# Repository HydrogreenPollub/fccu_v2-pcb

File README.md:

View this project on [CADLAB.io](https://cadlab.io/project/29095). 

# template-pcb

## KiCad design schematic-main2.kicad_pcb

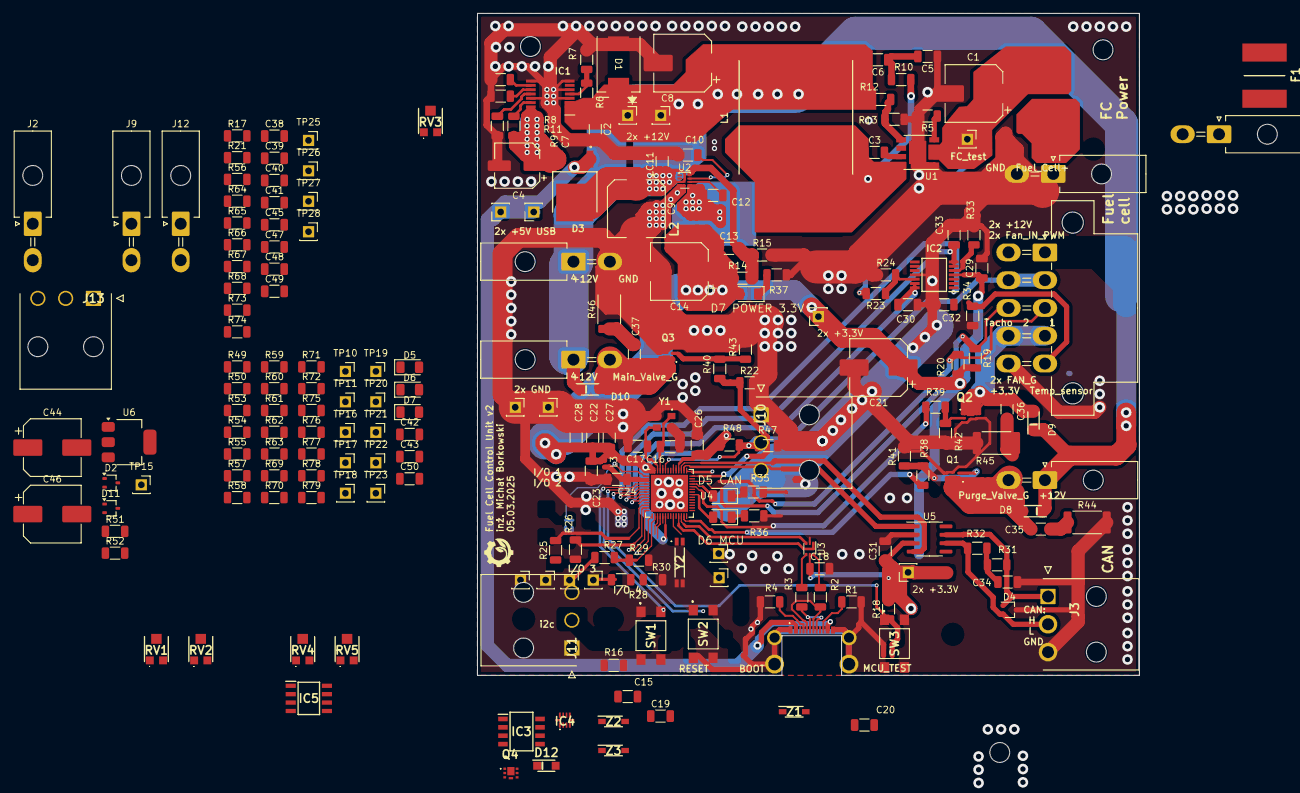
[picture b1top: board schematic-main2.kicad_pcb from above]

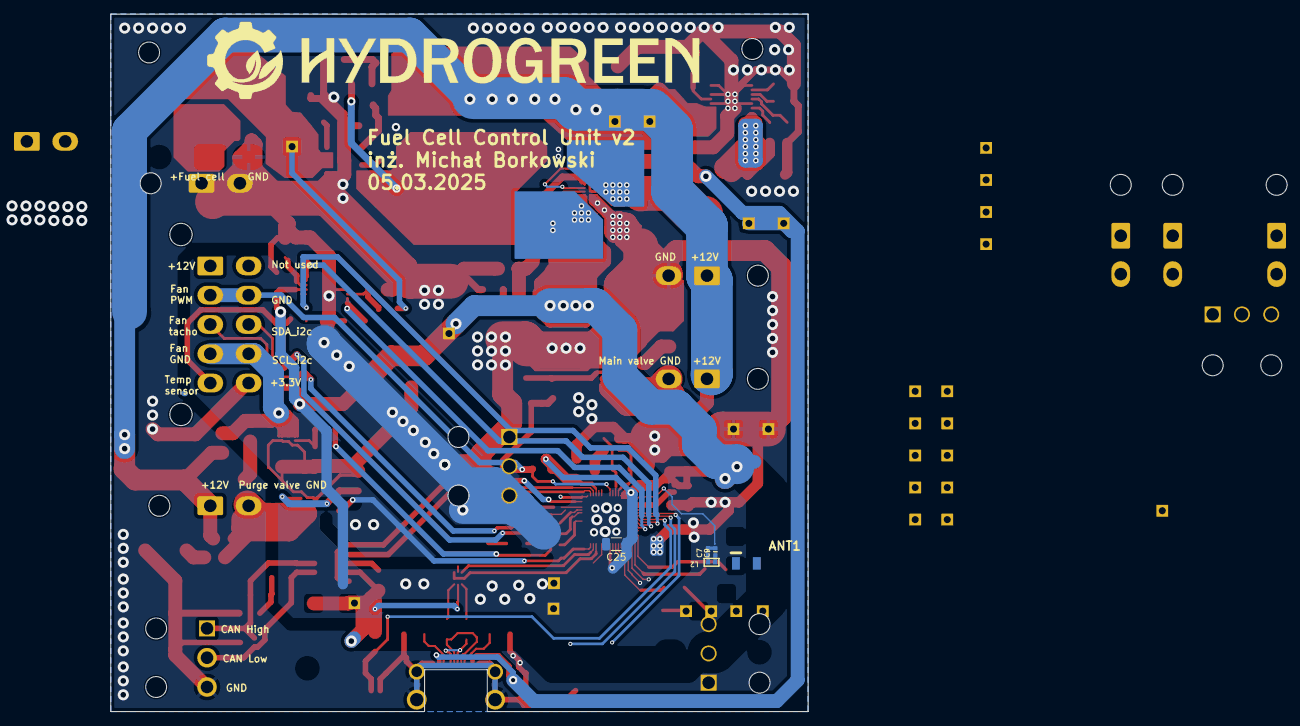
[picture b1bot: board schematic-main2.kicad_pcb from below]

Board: 2 copper layers, 100.0 x 100.0 mm, 224 parts (5 on the bottom side), 122 nets.

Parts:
ANT1: 2450AT18B100E; ANTC3216X140N
C1: 10u 100V; CP_Elec_8x10.5
C2, C22, C27, C39: 1u; C_1206_3216Metric
C3: 2n2 100V; C_1206_3216Metric
C4: 47u; CP_Elec_6.3x7.7
C5, C13: 47p; C_1206_3216Metric
C6: 3n3; C_1206_3216Metric
C7: 2n7; C_1206_3216Metric
C7#2: 2n7; _0402NO
C8, C44, C46: 22u; CP_Elec_8x10.5
C9, C21: 10u; CP_Elec_8x10.5
C9#2: 10u; _0402NO
C10: 33n; C_1206_3216Metric
C11, C12, C15, C18, C19, C20, C23, C24, C25, C26, C29, C31, C38, C43, C50: 100n; C_1206_3216Metric
C14: 100u; CP_Elec_8x10.5
C16, C17: 12p; C_1206_3216Metric
C28: 10n; C_1206_3216Metric
C30, C32, C33, C34, C42: 4n7; C_1206_3216Metric
C35, C36, C37: 20n; C_1206_3216Metric
C40, C41: 1p2; C_1206_3216Metric
C45, C47: 0; C_1206_3216Metric
C48, C49: 20p; C_1206_3216Metric
D1: TPSMC30CA; TPSMCSeries_LTF
D2, D11: V10K100DUHM3_H; SOT-323_SC-70
D3: V10K100DUHM3_H; TO252_(DPAK)_1
D4: SP0502BAJT; SOT-323_SC-70
D5, D5 CAN, D6, D6 MCU, D7, D7 POWER 3.3V: LED; LED_1206_3216Metric
D8, D9, D10: PMEG10020; PMEG10020ELR
D12: V10K100DUHM3_H; PMEG10020ELR
F1: 3A; FUSC8664X180N
IC1: LM76202QPWPRQ1; SOP65P640X120-17N
IC2: AD8544ARUZ-REEL; SOP65P640X120-14N
IC3: ILD206T; SOIC127P610X323-8N
IC4: TLA2024IRUGR; ADS7142IRUGT
IC5: 2EDN8534FXTMA1; SOIC127P602X173-8N
J1: Fuell_Cell; Molex_Mini-Fit_Jr_5569-02A2_2x01_P4.20mm_Horizontal
J2: Analog_In; Molex_Mini-Fit_Jr_5569-02A2_2x01_P4.20mm_Horizontal
J3: CAN; 39303035
J4: 12V_Out; Molex_Mini-Fit_Jr_5569-02A2_2x01_P4.20mm_Horizontal
J5, J9, J12: P_Valve; Molex_Mini-Fit_Jr_5569-02A2_2x01_P4.20mm_Horizontal
J6: M_Valve; Molex_Mini-Fit_Jr_5569-02A2_2x01_P4.20mm_Horizontal
J7: FC Cooling; Molex_Mini-Fit_Jr_5569-10A1_2x05_P4.20mm_Horizontal
J8: Supercapacitors; Molex_Mini-Fit_Jr_5569-02A2_2x01_P4.20mm_Horizontal
J10: UART; 39303035
J11: i2c; 39303035
J13: FC_Module; 39303035
L1: IHLP6767DZER470M11
L2: 4u7; SRN3015TA4R7M
L2#2: 4u7; _0402
L3: 2n; L_0402_1005Metric
P1: USB_C_Plug_USB2.0; 2169900002
Q1, Q2, Q3, Q4: PMPB10XNX; PMPB15XPAX
R1, R4: 5k1; R_1206_3216Metric
R2, R3: 0; R_1206_3216Metric
R5, R8, R9: 100k; R_1206_3216Metric
R6: 180k; R_1206_3216Metric
R7: 12k; R_1206_3216Metric
R10: 143k; R_1206_3216Metric
R11: 5k; R_1206_3216Metric
R12: 453k; R_1206_3216Metric
R13: 49k9; R_1206_3216Metric
R14: 47k; R_1206_3216Metric
R15, R34, R53, R54, R55, R79: 15k; R_1206_3216Metric
R16, R17, R18, R20, R22, R29, R30, R41, R42, R43, R47, R48, R56, R58, R59, R60, R61, R63, R66, R75, R76, R77, R78: 10k; R_1206_3216Metric
R19, R21, R74: 200R; R_1206_3216Metric
R23, R49: 6k8; R_1206_3216Metric
R24, R50: 3k3; R_1206_3216Metric
R25, R26, R33, R35, R36, R37, R69, R70, R71, R72: 1k; R_1206_3216Metric
R27, R28, R64, R65: 100R; R_1206_3216Metric
R31, R32: 60; R_1206_3216Metric
R38, R39, R40: 180R; R_1206_3216Metric
R44, R45, R46: 100R 0,5W; R_2512_6332Metric
R51, R52: 0R; R_1206_3216Metric
R57, R62: k; R_1206_3216Metric
R67, R68: 2k; R_1206_3216Metric
R73: 5M; R_1206_3216Metric
RV1: Pot_12V 20k; TC33X2503E
RV2: Pot_12V 5k; TC33X2503E
RV3, RV4, RV5: Pot_12V 2k; TC33X2503E
SW1, SW2, SW3: TL3305BF100QG; TL3305BF160QG
TP1, TP1#2, TP1#3, TP1#4: Vin test; PinSocket_1x01_P2.54mm_Vertical
TP2, TP2#2, TP3: GND; PinSocket_1x01_P2.54mm_Vertical
TP4, TP5: +12V; PinSocket_1x01_P2.54mm_Vertical
TP6, TP7: +5V; PinSocket_1x01_P2.54mm_Vertical
TP9, TP9#2: +3.3V; PinSocket_1x01_P2.54mm_Vertical
TP10: I/O 1; PinSocket_1x01_P2.54mm_Vertical
TP11: I/O 2; PinSocket_1x01_P2.54mm_Vertical
TP12: I/O 3; PinSocket_1x01_P2.54mm_Vertical
TP13: I/O 4; PinSocket_1x01_P2.54mm_Vertical
TP15: 5V; PinSocket_1x01_P2.54mm_Vertical
TP16: OP_1; PinSocket_1x01_P2.54mm_Vertical
TP17: OP_2; PinSocket_1x01_P2.54mm_Vertical
TP18: OP_3; PinSocket_1x01_P2.54mm_Vertical
TP19: OP_4; PinSocket_1x01_P2.54mm_Vertical
TP20: OP_8; PinSocket_1x01_P2.54mm_Vertical
TP21: OP_7; PinSocket_1x01_P2.54mm_Vertical
TP22: OP_6; PinSocket_1x01_P2.54mm_Vertical
TP23: OP_5; PinSocket_1x01_P2.54mm_Vertical
TP25: G14; PinSocket_1x01_P2.54mm_Vertical
TP26: G12; PinSocket_1x01_P2.54mm_Vertical
TP27: G42; PinSocket_1x01_P2.54mm_Vertical
TP28: G41; PinSocket_1x01_P2.54mm_Vertical
U1: LM5013DDAR; Diodes_SO-8EP
U2: TPS62933; SOT-583-8
U3: USBLC6-2P6; SOT-666
U4: ESP32-S3FN8; QFN-56-1EP_7x7mm_P0.4mm_EP5.6x5.6mm
U5: SN65HVD232; SOIC-8_3.9x4.9mm_P1.27mm
U6: LDI1117-05H; SOT-223-3_TabPin2
Y1: Crystal_GND24; KC3225K400000C1GE00
Y2: 9HT7-32.768KDZF-T; 9HT732768KDZFT
Z1, Z2, Z3: MMSZ3V3T1G; SOD3716X135N

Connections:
+3.3V: C13.1, C14.1, C18.1, C21.1, C22.1, C23.1, C25.1, C26.1, C27.1, C28.1, C29.1, C31.1, C38.1, C39.1, C43.1, C50.1, D7.2 (A), D7 POWER 3.3V.2 (A), IC2.4 (V+), IC4.8 (VDD), J2.1, L2.2, L2#2.2, L3.1, R14.1, R16.2, R17.2, R18.2, R20.2, R48.2, R59.1, R61.1, R67.2, R68.2, TP9.1, TP9#2.1, U3.5 (VBUS), U4.20 (VDD3P3_RTC), U4.29 (VDD_SPI), U4.46 (VDD3P3_CPU), U4.55 (VDDA), U4.56 (VDDA), U5.3 (VCC)
+5V: TP6.1, TP7.1, TP15.1
+12V: C2.1, C6.2, C8.1, D1.2 (A), D8.1 (K), D9.1 (K), D10.1 (K), IC1.1 (IN_1), IC1.2 (IN_2), IC1.3 (UVLO), J4.1, J5.1, J6.1, J7.1, L1.2, R6.1, R12.2, TP4.1, TP5.1
/IO/CANH: D4.1 (K), J3.1, R31.2, U5.7 (CANH)
/IO/CANL: D4.2 (K), J3.2, R32.2, U5.6 (CANL)
/IO/CAN_RX: U4.44 (MTCK/JTAG/GPIO39), U5.1 (D)
/IO/CAN_TX: U4.45 (MTDO/JTAG/GPIO40), U5.4 (R)
/IO/FAN_ON: C36.1, D9.2 (A), Q2.1 (D)
/IO/FC_V: J1.2, R23.2, R52.1
/IO/FC_VOLTAGE_MCU: C30.2, IC2.13 (-IN_D), IC2.14 (OUT_D)
/IO/I/O_3_MCU: R27.2, R29.1
/IO/I/O_4_MCU: R28.2, R30.1
/IO/LED_CAN_STATUS: D5.2 (A), D5 CAN.2 (A)
/IO/LED_MCU_STATUS: D6.2 (A), D6 MCU.2 (A)
/IO/LP_MCU: C32.2, IC2.1 (OUT_A), R57.1
/IO/Main_Valve: C37.1, D10.2 (A), J6.2, Q3.1 (D)
/IO/PURGE_VALVE: C35.1, D8.2 (A), J5.2, Q1.1 (D)
/IO/SC_VOLTAGE_MCU: C42.2, IC2.8 (OUT_C), IC2.9 (-IN_C)
/IO/TEMP_SENSOR: IC2.5 (+IN_B), R59.2
/IO/Temp_MCU: C33.1, IC2.7 (OUT_B), R60.2
/MCU/BOOT: C19.1, SW2.3 (K), SW2.4 (A), U4.5 (GPIO0/BOOT)
/MCU/BUTTON_MCU_G36: J9.1, R21.2
/MCU/FAN_IN_PWM_MCU_G45: R47.1, R48.1, R74.1
/MCU/MAIN_VALVE_MCU_G37: R22.1, U4.42 (GPIO37)
/MCU/MCU_TEST: C20.1, R56.2, SW3.1, SW3.2
/MCU/RESET: C15.1, R16.1, SW1.3 (K), SW1.4 (A), U4.4 (CHIP_PU/RESET)
/MCU/Rx_G44: J10.1, R65.2
/MCU/SCL_G10: J11.1, R68.1, U4.15 (GPIO10/ADC1_CH9)
/MCU/SDA_G9: J11.2, R67.1, U4.14 (GPIO9/ADC1_CH8)
/MCU/Tx_G43: J10.2, R64.1
/MCU/U1_VOLTAGE_G6: J12.1, R66.2
/MCU/USB_D+: R3.2, U3.3 (I/O2), U3.4 (I/O2), U4.26 (GPIO20/USB_D+/ADC2_CH9)
/MCU/USB_D-: R2.2, U3.1 (I/O1), U3.6 (I/O1), U4.25 (GPIO19/USB_D-/ADC2_CH8)
/MCU/XTAL_N: C16.1, U4.53 (XTAL_N), Y1.1
/MCU/XTAL_N_32: C48.1, R73.1, U4.22 (GPIO16/ADC2_CH5/XTAL_32K_N), Y2.4 (X2)
/MCU/XTAL_P: C17.1, U4.54 (XTAL_P), Y1.3
/MCU/XTAL_P_32: C49.1, R73.2, U4.21 (GPIO15/ADC2_CH4/XTAL_32K_P), Y2.1 (X1)
/Power /FB_12: RV1.2, U1.5 (FB)
/Power /Vreg: C4.1, C44.1, D11.1, D11.2, IC1.15 (OUT_1), IC1.16 (OUT_2), R9.1, U6.3 (VI)
/VBUS: D11.3, J8.2, P1.A4 (VBUS), P1.A9 (VBUS), P1.B4 (VBUS), P1.B9 (VBUS), R49.2, R51.1
GND: C1.2, C2.2, C4.2, C5.1, C7.2, C7#2.2, C8.2, C9.2, C9#2.2, C10.2, C11.2, C14.2, C15.2, C16.2, C17.2, C18.2, C19.2, C20.2, C21.2, C22.2, C23.2, C24.2, C25.2, C26.2, C27.2, C28.2, C29.2, C30.1, C31.2, C32.1, C33.2, C34.2, C38.2, C39.2, C40.1, C41.2, C42.1, C43.2, C44.2, C45.2, C46.2, C47.2, C48.2, C49.2, C50.2, D1.1 (K), D2.1, D2.2, D2.3, D4.3 (A), IC1.4 (NC_1), IC1.6 (MODE), IC1.8 (RTN), IC1.9 (GND), IC1.13 (NC_2), IC1.17 (EP), IC2.11 (GND), IC4.1 (ADDR), IC4.3 (GND), J1.1, J3.3, J4.2, J7.10, J8.1, J9.2, J10.3, J11.3, J12.2, P1.A1 (GND), P1.A12 (GND), P1.B1 (GND), P1.B12 (GND), Q1.3 (S), Q2.3 (S), Q3.3 (S), Q4.3 (S), R1.2, R4.2, R5.2, R7.2, R8.2, R11.2, R13.1, R15.2, R22.2, R24.1, R29.2, R30.2, R33.2, R34.2, R35.2, R36.2, R37.2, R41.2, R42.2, R43.2, R44.2, R45.2, R46.2, R47.2, R50.1, R53.2, R54.2, R55.2, R56.1, R58.2, R62.2, R79.2, SW1.1, SW1.2, SW2.1, SW2.2, TP2.1, TP2#2.1, TP3.1, U1.1 (GND), U1.9 (EP), U2.4 (GND), U3.2 (GND), U4.57 (GND), U5.2 (GND), U6.1 (GND), Y1.2, Y1.4, Y2.2 (GND_1), Y2.3 (GND_2), Z1.2 (A), Z2.2 (A), Z3.2 (A)
unnamed: ANT1.1 (FEED), C40.2
unnamed: C5.2, C6.1, R10.2
unnamed: C34.1, R31.1, R32.1
unnamed: C35.2, R44.1
unnamed: C36.2, R45.1
unnamed: C37.2, R46.1
unnamed: D3.1, D3.2, R52.2
unnamed: D3.3, R51.2
unnamed: D5.1 (K), D5 CAN.1 (K), R35.1
unnamed: D6.1 (K), D6 MCU.1 (K), R36.1
unnamed: D7.1 (K), D7 POWER 3.3V.1 (K), R37.1
unnamed: C7.1, C7#2.1, IC1.12 (DVDT)
unnamed: IC1.11 (ILIM), RV3.2
unnamed: IC1.10 (IMON), R8.1
unnamed: IC1.5 (OVP), R6.2, R7.1
unnamed: IC1.14 (~FLT), R9.2
unnamed: IC2.3 (+IN_A), R34.1, R63.2
unnamed: IC2.10 (+IN_C), RV4.2
unnamed: IC2.12 (+IN_D), RV5.2
unnamed: IC2.2 (-IN_A), R57.2, R62.1
unnamed: IC2.6 (-IN_B), R58.1, R60.1
unnamed: IC3.1 (A_1), R69.2
unnamed: IC3.3 (A_2), R70.2
unnamed: IC3.6 (C_3), R72.1
unnamed: IC3.8 (C_4), R71.1
unnamed: IC3.5 (E_1), TP23.1
unnamed: IC3.7 (E_2), TP21.1
unnamed: IC3.2 (K_1), TP17.1
unnamed: IC3.4 (K_2), TP19.1
unnamed: IC4.4 (AIN0), R78.2, R79.1
unnamed: IC4.5 (AIN1), R53.1, R75.2
unnamed: IC4.6 (AIN2), R54.1, R76.2
unnamed: IC4.7 (AIN3), R55.1, R77.2
unnamed: P1.A5 (CC), R4.1
unnamed: P1.A6 (D+), P1.B6 (D+), R3.1
unnamed: P1.A7 (D-), P1.B7 (D-), R2.1
unnamed: P1.B5 (VCONN), R1.1
unnamed: Q1.2 (G), R38.1, R41.1
unnamed: Q2.2 (G), R39.1, R42.1
unnamed: Q3.2 (G), R40.1, R43.1
unnamed: R11.1, RV3.1
unnamed: R12.1, RV1.3
unnamed: R13.2, RV1.1
unnamed: R14.2, RV2.3
unnamed: R15.1, RV2.1
unnamed: R23.1, RV5.1
unnamed: R24.2, RV5.3
unnamed: R25.1, TP10.1
unnamed: R26.1, TP11.1
unnamed: R27.1, TP12.1
unnamed: R28.1, TP13.1
unnamed: R33.1, R61.2
unnamed: R49.1, RV4.1
unnamed: R50.2, RV4.3
unnamed: R69.1, TP16.1
unnamed: R70.1, TP18.1
unnamed: R71.2, TP20.1
unnamed: R72.2, TP22.1
unnamed: R18.1, SW3.3 (K), SW3.4 (A)
unnamed: C3.2, U1.7 (BST)
unnamed: C1.1, F1.2, TP1.1, TP1#2.1, TP1#3.1, TP1#4.1, U1.2 (VIN), U1.3 (EN_UVLO)
unnamed: R5.1, U1.4 (RON)
unnamed: C3.1, L1.1, R10.1, U1.8 (SW)
unnamed: C12.1, U2.6 (BST)
unnamed: C13.2, RV2.2, U2.8 (FB)
unnamed: C10.1, U2.7 (SS)
unnamed: C12.2, L2.1, L2#2.1, U2.5 (SW)
unnamed: C9.1, C9#2.1, C11.1, U2.3 (VIN)
unnamed: C45.1, R66.1, U4.11 (GPIO6/ADC1_CH5), Z2.1 (K)
unnamed: TP26.1, U4.17 (GPIO12/ADC2_CH1)
unnamed: TP25.1, U4.19 (GPIO14/ADC2_CH3)
unnamed: R17.1, R19.1, U4.40 (GPIO35), Z3.1 (K)
unnamed: C47.1, R20.1, R21.1, U4.41 (GPIO36), Z1.1 (K)
unnamed: R74.2, U4.51 (GPIO45)
unnamed: C41.1, U4.1 (LNA_IN/RF)
unnamed: TP28.1, U4.47 (MTDI/JTAG/GPIO41)
unnamed: TP27.1, U4.48 (MTMS/JTAG/GPIO42)
unnamed: R65.1, U4.50 (U0RXD/PROG/GPIO44)
unnamed: R64.2, U4.49 (U0TXD/PROG/GPIO43)
unnamed: C46.1, D12.1, D12.2, U6.2 (VO)
VDD3P3: C24.1, L3.2, U4.2 (VDD3P3), U4.3 (VDD3P3)

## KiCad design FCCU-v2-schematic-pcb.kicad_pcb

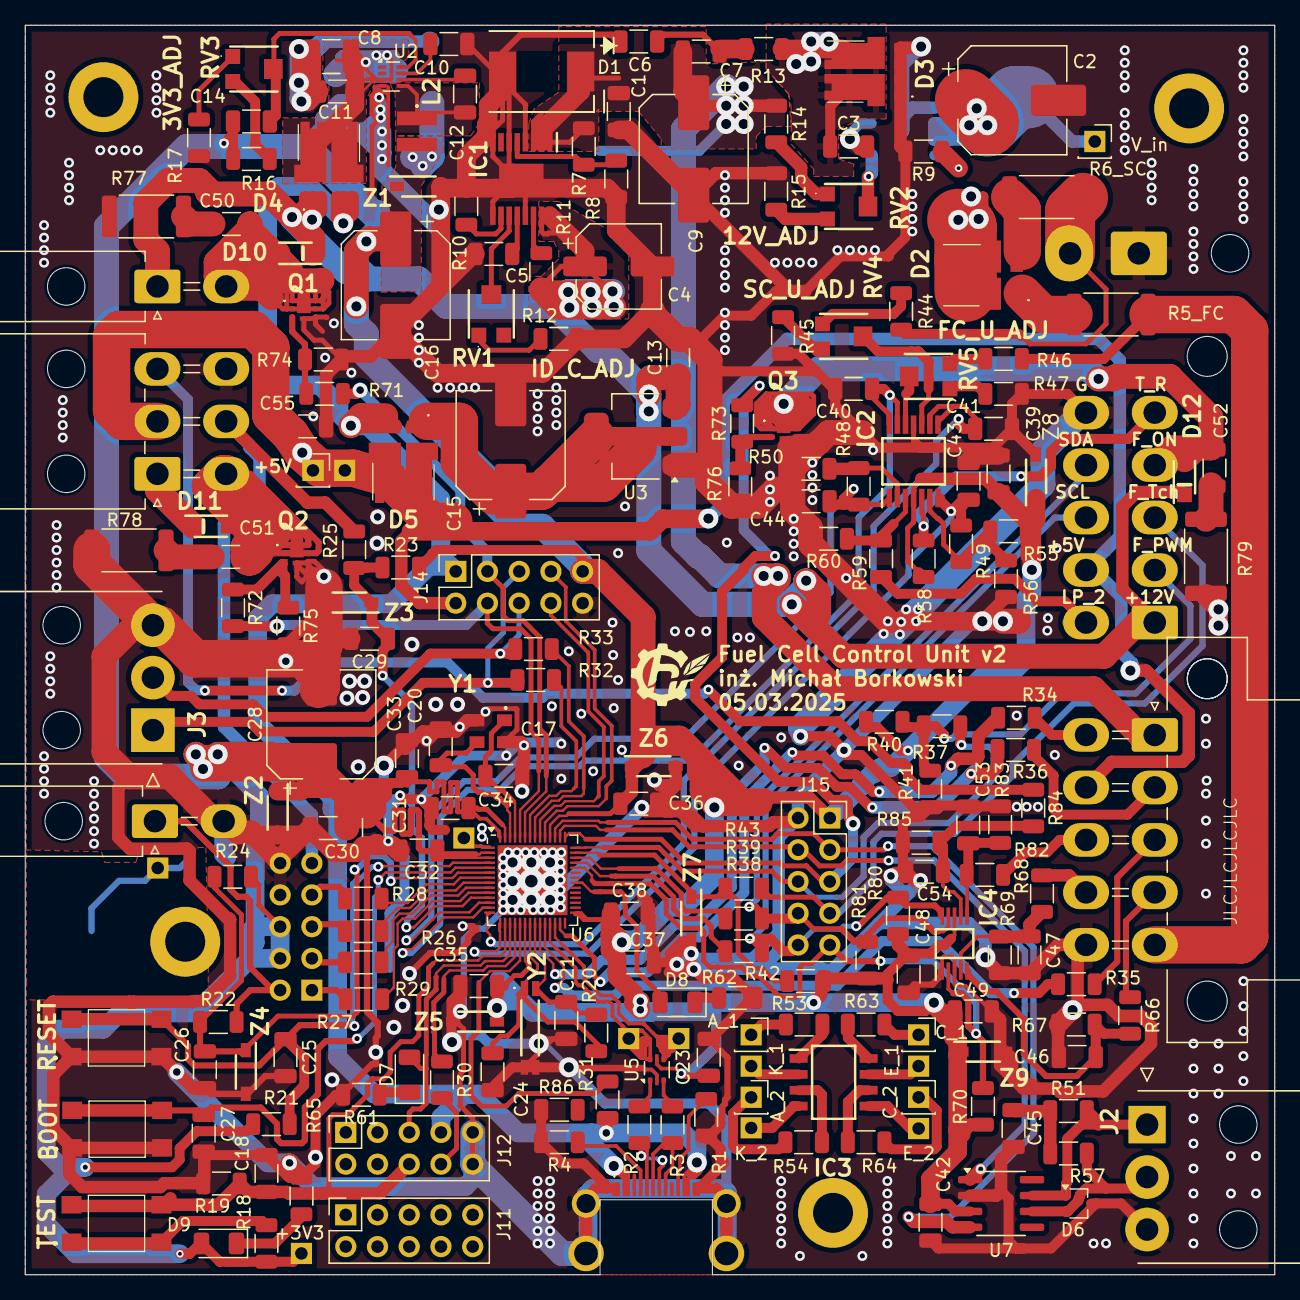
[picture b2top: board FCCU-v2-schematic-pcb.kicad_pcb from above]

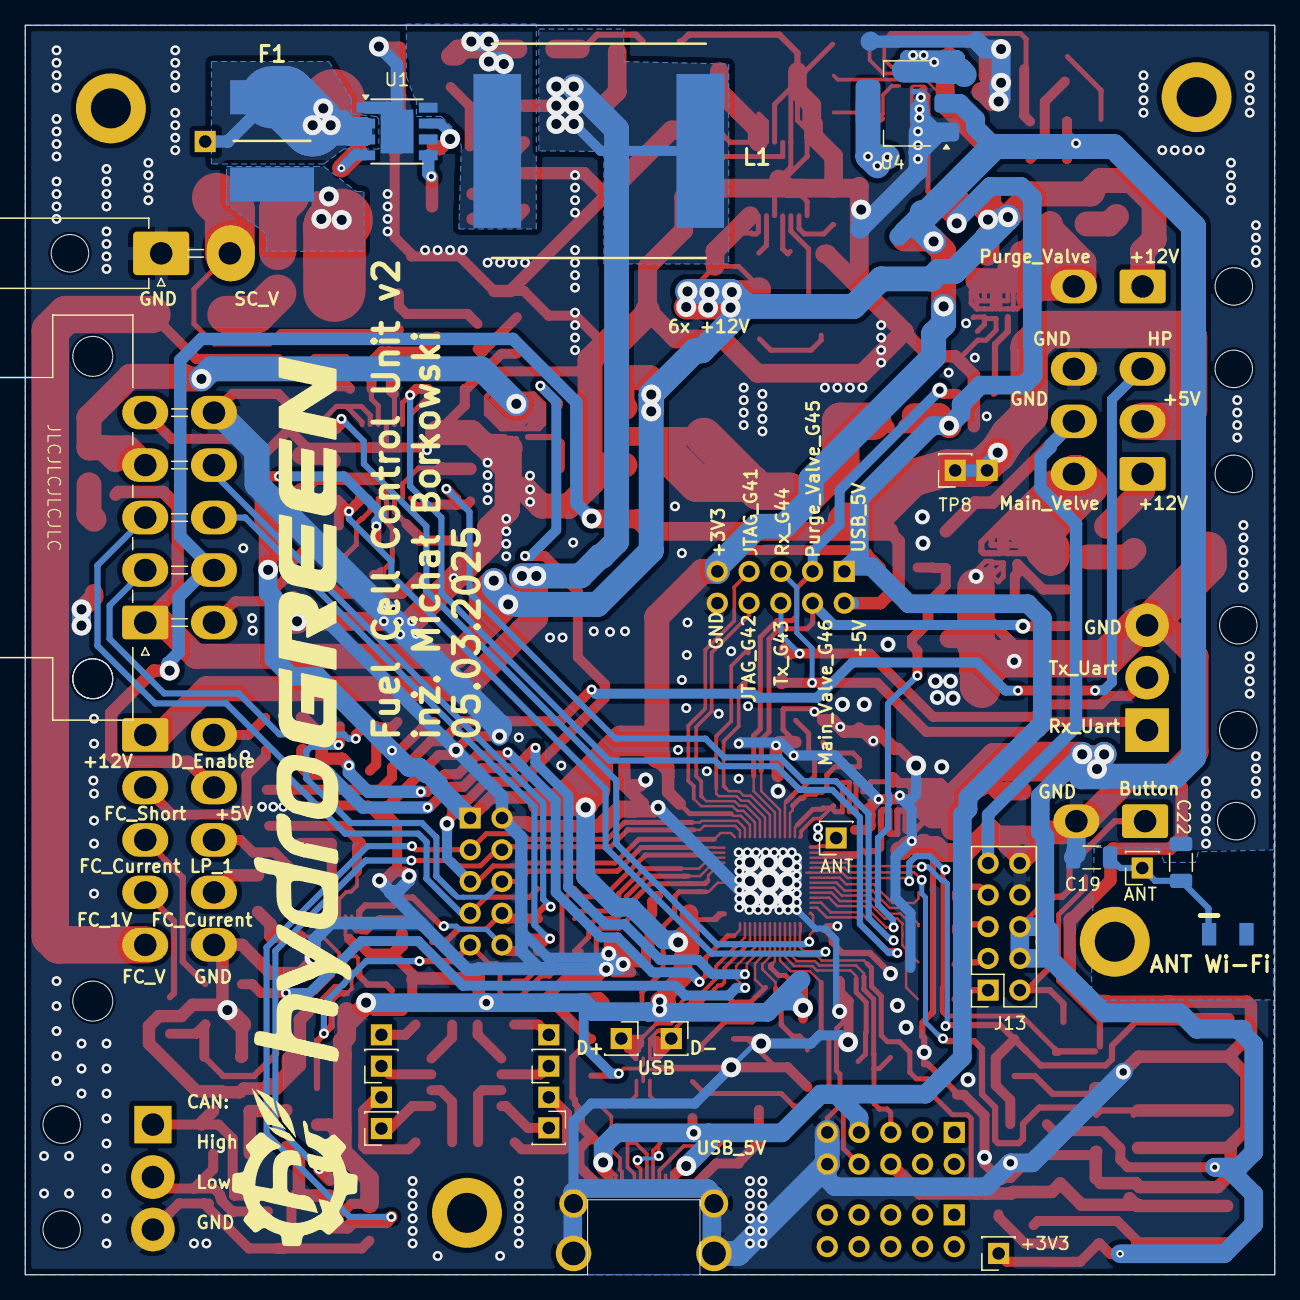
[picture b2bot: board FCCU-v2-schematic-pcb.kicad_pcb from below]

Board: 2 copper layers, 100.0 x 100.0 mm, 219 parts (20 on the bottom side), 142 nets.

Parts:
+3V3: +3.3V; PinSocket_1x01_P2.54mm_Vertical
+5V: +5V; PinSocket_1x01_P2.54mm_Vertical
ANT: Ant; PinSocket_1x01_P2.54mm_Vertical
ANT Wi-Fi: 2450AT18B100E; ANTC3216X140N
A_1: A_1; PinSocket_1x01_P2.54mm_Vertical
A_2: A_2; PinSocket_1x01_P2.54mm_Vertical
BOOT: TL3305BF100QG; TL3305BF160QG
C1, C13, C30, C33, C38, C55: 1u; C_1206_3216Metric
C2: 10u 100V; CP_Elec_8x10.5
C3: 2n2 100V; C_1206_3216Metric
C4: 47u; CP_Elec_6.3x7.7
C5: 2n7; C_1206_3216Metric
C6, C14: 47p; C_1206_3216Metric
C7: 3n3; C_1206_3216Metric
C8: 1-10u; C_1210_3225Metric_Pad1.33x2.70mm_HandSolder
C9, C15: 22u; CP_Elec_8x10.5
C10: 33n; C_1206_3216Metric
C11, C12, C18, C23, C25, C27, C31, C32, C35, C36, C37, C39, C42, C48: 100n; C_1206_3216Metric
C16: 100u; CP_Elec_8x10.5
C17, C20: 12p; C_1206_3216Metric
C19, C22: 1p2; C_1206_3216Metric
C21, C24: 20p; C_1206_3216Metric
C26, C29: 0; C_1206_3216Metric
C28: 10u; CP_Elec_8x10.5
C34: 10n; C_1206_3216Metric
C40, C41, C44, C46, C47, C53, C54: c; C_1206_3216Metric
C43, C45: 4n7; C_1206_3216Metric
C49: 4N7; C_1206_3216Metric
C50, C51, C52: 20n; C_1206_3216Metric
C_1: C_1; PinSocket_1x01_P2.54mm_Vertical
C_2: C_2; PinSocket_1x01_P2.54mm_Vertical
D1: TPSMC30CA; TPSMCSeries_LTF
D2, D3, D4, D5: V10K100DUHM3_H; V10K100DUHM3H
D6: SP0502BAJT; SOT-323_SC-70
D7, D8, D9: LED; LED_1206_3216Metric
D10, D11, D12: PMEG10020; PMEG10020ELR
E_1: E_1; PinSocket_1x01_P2.54mm_Vertical
E_2: E_2; PinSocket_1x01_P2.54mm_Vertical
F1: 3A; FUSC8664X180N
IC1: LM76202QPWPRQ1; SOP65P640X120-17N
IC2: AD8544ARUZ-REEL; SOP65P640X120-14N
IC3: ILD206T; SOIC127P610X323-8N
IC4: ADS1015IDGSR; SOP50P490X110-10N
J1: Supercapacitors; Molex_Mini-Fit_Jr_5569-02A2_2x01_P4.20mm_Horizontal
J2: CAN; 39303035
J3: UART; 39303035
J4: P_Valve; Molex_Mini-Fit_Jr_5569-02A2_2x01_P4.20mm_Horizontal
J5: Button; Molex_Mini-Fit_Jr_5569-02A2_2x01_P4.20mm_Horizontal
J6: FC Module; Molex_Mini-Fit_Jr_5569-10A1_2x05_P4.20mm_Horizontal
J7: FC Cooling; Molex_Mini-Fit_Jr_5569-10A1_2x05_P4.20mm_Horizontal
J8: M_Valve; Molex_Mini-Fit_Jr_5569-06A2_2x03_P4.20mm_Horizontal
J11: NC; PinSocket_2x05_P2.54mm_Vertical
J12: Analog; PinSocket_2x05_P2.54mm_Vertical
J13: I/O; PinSocket_2x05_P2.54mm_Vertical
J14: Top signals; PinSocket_2x05_P2.54mm_Vertical
J15: Fuel cell signals; PinSocket_2x05_P2.54mm_Vertical
K_1: K_1; PinSocket_1x01_P2.54mm_Vertical
K_2: K_2; PinSocket_1x01_P2.54mm_Vertical
L1: IHLP6767DZER470M11
L2: 4u7; SRN3015TA4R7M
P1: USB_C_Plug_USB2.0; 2169900002
Q1, Q2, Q3: PMPB10XNX; PMPB15XPAX
R1, R4: 5k1; R_1206_3216Metric
R2, R3: 0; R_1206_3216Metric
R5_FC, R6_SC: 0R; R_2512_6332Metric
R7: 180k; R_1206_3216Metric
R8: 12k; R_1206_3216Metric
R9, R10, R11: 100k; R_1206_3216Metric
R12: 5k6; R_1206_3216Metric
R13: 143k; R_1206_3216Metric
R14: 453k; R_1206_3216Metric
R15: 49k9; R_1206_3216Metric
R16: 47k; R_1206_3216Metric
R17, R60, R67, R69, R83, R85, R86: 15k; R_1206_3216Metric
R18, R19, R21, R23, R24, R31, R40, R41, R42, R49, R55, R58, R59, R66, R68, R74, R75, R76, R82, R84: 10k; R_1206_3216Metric
R20: 5M; R_1206_3216Metric
R22, R25, R26, R27, R28, R29, R30, R34, R35, R36, R43, R53, R54, R56, R61, R62, R63, R64, R65: 1k; R_1206_3216Metric
R32, R33: 100R; R_1206_3216Metric
R37: 200R; R_1206_3216Metric
R38, R39: 0R; R_1206_3216Metric
R44, R46: 6k8; R_1206_3216Metric
R45, R47: 3k3; R_1206_3216Metric
R48, R50: k; R_1206_3216Metric
R51, R57: 60; R_1206_3216Metric
R70, R80, R81: 2k; R_1206_3216Metric
R71, R72, R73: 180R; R_1206_3216Metric
R77, R78, R79: 100R 0,5W; R_2512_6332Metric
RESET: TL3305BF100QG; TL3305BF160QG
RV1, RV2: Pot_12V 20k; TC33X2503E
RV3: Pot_12V 5k; TC33X2503E
RV4, RV5: Pot_12V 2k; TC33X2503E
TEST: TL3305BF100QG; TL3305BF160QG
TP3: Ant; PinSocket_1x01_P2.54mm_Vertical
TP8: +5V; PinSocket_1x01_P2.54mm_Vertical
TP12: USB_D+; PinSocket_1x01_P2.54mm_Vertical
TP13: USB_D-; PinSocket_1x01_P2.54mm_Vertical
U1: LM5013DDAR; Diodes_SO-8EP
U2: TPS62933; SOT-583-8
U3: LDI1117-05H; SOT-223-3_TabPin2
U4: LDI1117-3.3H; SOT-223-3_TabPin2
U5: USBLC6-2P6; SOT-666
U6: ESP32-S3FN8; QFN-56-1EP_7x7mm_P0.4mm_EP5.6x5.6mm
U7: SN65HVD232; SOIC-8_3.9x4.9mm_P1.27mm
V_in: Vin test; PinSocket_1x01_P2.54mm_Vertical
Y1: Crystal_GND24; KC3225K400000C1GE00
Y2: 9HT7-32.768KDZF-T; 9HT732768KDZFT
Z1, Z2, Z3, Z4, Z5, Z6, Z7, Z8, Z9: MMSZ3V3T1G; SOD3716X135N

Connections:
+3.3V: +3V3.1, C14.1, C16.1, C23.1, C28.1, C30.1, C31.1, C32.1, C33.1, C34.1, C35.1, C36.1, C37.1, C38.1, C39.1, C42.1, C48.1, C49.1, D9.2 (A), IC2.4 (V+), IC4.8 (VDD), J13.7, J13.8, J14.5, J15.1, L2.2, R16.1, R18.2, R21.2, R23.2, R24.2, R40.2, R42.2, R55.1, R58.1, R70.1, R80.1, R81.1, U4.2 (VO), U5.5 (VBUS), U6.2 (VDD3P3), U6.3 (VDD3P3), U6.20 (VDD3P3_RTC), U6.29 (VDD_SPI), U6.46 (VDD3P3_CPU), U6.55 (VDDA), U6.56 (VDDA), U7.3 (VCC), Z1.1 (K), Z2.1 (K), Z5.1 (K), Z6.1 (K), Z8.1 (K), Z9.1 (K)
+5V: +5V.1, C55.1, D5.5, D5.6, D5.7, D5.8, J6.7, J7.7, J8.2, J14.6, TP8.1
+12V: C4.1, C13.1, D4.1, D4.2, D10.1 (K), D11.1 (K), D12.1 (K), IC1.15 (OUT_1), IC1.16 (OUT_2), J4.1, J7.1, J8.1, R11.1, U3.3 (VI)
/12V_no_id: C1.1, C7.2, C9.1, D1.2 (A), IC1.1 (IN_1), IC1.2 (IN_2), IC1.3 (UVLO), J6.1, L1.2, R7.1, R14.2
/IO/CANH: D6.1 (K), J2.1, R51.2, U7.7 (CANH)
/IO/CANL: D6.2 (K), J2.2, R57.2, U7.6 (CANL)
/IO/CAN_RX: J15.7, U6.44 (MTCK/JTAG/GPIO39), U7.1 (D)
/IO/CAN_TX: J15.2, U6.45 (MTDO/JTAG/GPIO40), U7.4 (R)
/IO/FAN_IN_PWM: J7.2, R37.1, R40.1, R41.1
/IO/FAN_ON: C52.1, D12.2 (A), J7.4, Q3.1 (D)
/IO/FAN_ON_MCU: J15.3, R73.2, U6.43 (GPIO38)
/IO/FAN_TACHO: J7.3, J15.4, R43.2
/IO/FC_1V: J6.4, R66.1
/IO/FC_C: J6.9, R68.1
/IO/FC_V: J6.5, R5_FC.1, R46.2
/IO/FC_VOLTAGE_MCU: C40.2, IC2.13 (-IN_D), IC2.14 (OUT_D), U6.13 (GPIO8/ADC1_CH7)
/IO/HP: J8.3, R84.1
/IO/I/O_5_MCU_G13: J8.5, J13.5, R25.1
/IO/LED_CAN_STATUS: D7.2 (A), J12.3, U6.17 (GPIO12/ADC2_CH1)
/IO/LED_RESTART_STATUS: D8.2 (A), U6.35 (SPID/GPIO32)
/IO/LP_1: J6.8, R82.1
/IO/LP_2: J7.6, R59.1
/IO/LP_MCU: C44.2, IC2.1 (OUT_A), R48.1, U6.12 (GPIO7/ADC1_CH6)
/IO/MAIN_VALVE_MCU: J14.7, R72.2, U6.52 (GPIO46)
/IO/Main_Valve: C51.1, D11.2 (A), J8.4, Q2.1 (D)
/IO/PURGE_VALVE: C50.1, D10.2 (A), J4.2, Q1.1 (D)
/IO/PURGE_VALVE_MCU: J14.2, R71.2, U6.51 (GPIO45)
/IO/RDY_MCU: IC4.2 (ALERT/RDY), J15.5, R70.2, U6.38 (GPIO33)
/IO/SCL_FC: IC4.10 (SCL), J7.8, J15.10, R38.2, R80.2
/IO/SC_V: J1.2, R6_SC.1, R44.2
/IO/SC_VOLTAGE_MCU: C41.2, IC2.8 (OUT_C), IC2.9 (-IN_C), U6.14 (GPIO9/ADC1_CH8)
/IO/SDA_FC: IC4.9 (SDA), J7.9, J15.9, R39.2, R81.2
/IO/TEMP_SENSOR: IC2.5 (+IN_B), J7.5, R58.2
/IO/Temp_MCU: C43.1, IC2.7 (OUT_B), R49.2, U6.15 (GPIO10/ADC1_CH9)
/MCU/Antena: ANT.1, C22.1, TP3.1, U6.1 (LNA_IN/RF)
/MCU/BOOT: BOOT.3 (K), BOOT.4 (A), C27.1, U6.5 (GPIO0/BOOT)
/MCU/BUTTON_MCU_G36: J5.1, J13.6, R22.2
/MCU/DRIVER_ENABLE_G17: J6.6, R34.1
/MCU/FAN_PWM: J15.8, R37.2, U6.42 (GPIO37)
/MCU/FC_CURRENT_PWM_G18: J6.3, R35.1
/MCU/FC_SHORT_MCU_G38: J6.2, R36.1
/MCU/I/O_1_MCU_G7: J13.4, R28.2
/MCU/I/O_2_MCU_G8: J13.3, R26.2
/MCU/I/O_3_MCU_G11: J13.2, R29.2
/MCU/I/O_4_MCU_G13: J13.1, R27.2
/MCU/I/O_6_MCU: J12.9, R30.2
/MCU/JTAG_G41: J14.4, U6.47 (MTDI/JTAG/GPIO41)
/MCU/JTAG_G42: J14.9, U6.48 (MTMS/JTAG/GPIO42)
/MCU/MCU_TEST_G1: C18.1, J12.8, R19.2, TEST.3 (K), TEST.4 (A), U6.16 (GPIO11/ADC2_CH0)
/MCU/RESET: C25.1, R21.1, RESET.3 (K), RESET.4 (A), U6.4 (CHIP_PU/RESET)
/MCU/Rx_G44: J3.1, J14.3, R32.2
/MCU/Tx_G43: J3.2, J14.8, R33.1
/MCU/USB_D+: R3.2, TP12.1, U5.3 (I/O2), U5.4 (I/O2), U6.26 (GPIO20/USB_D+/ADC2_CH9)
/MCU/USB_D-: R2.2, TP13.1, U5.1 (I/O1), U5.6 (I/O1), U6.25 (GPIO19/USB_D-/ADC2_CH8)
/MCU/XTAL_N: C17.1, U6.53 (XTAL_N), Y1.1
/MCU/XTAL_N_32: C21.1, R20.1, U6.22 (GPIO16/ADC2_CH5/XTAL_32K_N), Y2.4 (X2)
/MCU/XTAL_P: C20.1, U6.54 (XTAL_P), Y1.3
/MCU/XTAL_P_32: C24.1, R20.2, U6.21 (GPIO15/ADC2_CH4/XTAL_32K_P), Y2.1 (X1)
/Power /3V3_reg_in: C8.1, C11.1, D4.5, D4.6, D4.7, D4.8, U2.3 (VIN), U4.3 (VI)
/Power /FB_12: RV2.2, U1.5 (FB)
/VBUS: D4.3, D4.4, D5.3, D5.4, J12.4, J14.1, P1.A4 (VBUS), P1.A9 (VBUS), P1.B4 (VBUS), P1.B9 (VBUS), R31.2
GND: BOOT.1, BOOT.2, C1.2, C2.2, C4.2, C5.2, C6.1, C8.2, C9.2, C10.2, C11.2, C13.2, C15.2, C16.2, C17.2, C18.2, C19.1, C20.2, C21.2, C22.2, C23.2, C24.2, C25.2, C26.2, C27.2, C28.2, C29.2, C30.2, C31.2, C32.2, C33.2, C34.2, C35.2, C36.2, C37.2, C38.2, C39.2, C40.1, C41.1, C42.2, C43.2, C44.1, C45.2, C46.2, C47.2, C48.2, C49.2, C53.2, C54.2, C55.2, D1.1 (K), D3.1, D3.2, D3.3, D3.4, D6.3 (A), IC1.4 (NC_1), IC1.6 (MODE), IC1.8 (RTN), IC1.9 (GND), IC1.13 (NC_2), IC1.17 (EP), IC2.11 (GND), IC4.1 (ADDR), IC4.3 (GND), J1.1, J2.3, J3.3, J5.2, J6.10, J7.10, J8.6, J12.5, J12.10, J13.9, J13.10, J14.10, J15.6, P1.A1 (GND), P1.A12 (GND), P1.B1 (GND), P1.B12 (GND), Q1.3 (S), Q2.3 (S), Q3.3 (S), R1.2, R4.2, R8.2, R9.2, R10.2, R12.2, R15.1, R17.2, R19.1, R41.2, R45.1, R47.1, R50.2, R56.2, R60.2, R61.2, R62.2, R65.2, R67.2, R69.2, R74.2, R75.2, R76.2, R77.2, R78.2, R79.2, R83.2, R85.2, R86.1, RESET.1, RESET.2, U1.1 (GND), U1.9 (EP), U2.4 (GND), U3.1 (GND), U4.1 (GND), U5.2 (GND), U6.57 (GND), U7.2 (GND), Y1.2, Y1.4, Y2.2 (GND_1), Y2.3 (GND_2), Z1.2 (A), Z2.2 (A), Z3.2 (A), Z4.2 (A), Z5.2 (A), Z6.2 (A), Z7.2 (A), Z8.2 (A), Z9.2 (A)
unnamed: ANT Wi-Fi.1 (FEED), C19.2
unnamed: A_1.1, R53.1
unnamed: A_2.1, R54.1
unnamed: C6.2, C7.1, R13.2
unnamed: C45.1, R51.1, R57.1
unnamed: C50.2, R77.1
unnamed: C51.2, R78.1
unnamed: C52.2, R79.1
unnamed: C_1.1, R63.2
unnamed: C_2.1, R64.2
unnamed: D2.1, D2.2, R5_FC.2
unnamed: D2.3, D2.4, R6_SC.2
unnamed: D2.5, D2.6, D2.7, D2.8, F1.1
unnamed: D7.1 (K), R61.1
unnamed: D8.1 (K), R62.1
unnamed: D9.1 (K), R65.1
unnamed: C5.1, IC1.12 (DVDT)
unnamed: IC1.11 (ILIM), RV1.2
unnamed: IC1.10 (IMON), R10.1
unnamed: IC1.5 (OVP), R7.2, R8.1
unnamed: IC1.14 (~FLT), R11.2
unnamed: IC2.3 (+IN_A), R59.2, R60.1
unnamed: IC2.10 (+IN_C), RV4.2
unnamed: IC2.12 (+IN_D), RV5.2
unnamed: IC2.2 (-IN_A), R48.2, R50.1
unnamed: IC2.6 (-IN_B), R49.1, R55.2, R56.1
unnamed: IC3.1 (A_1), R53.2
unnamed: IC3.3 (A_2), R54.2
unnamed: IC3.8 (C_1), R63.1
unnamed: IC3.6 (C_2), R64.1
unnamed: E_1.1, IC3.7 (E_1)
unnamed: E_2.1, IC3.5 (E_2)
unnamed: IC3.2 (K_1), K_1.1
unnamed: IC3.4 (K_2), K_2.1
unnamed: C47.1, IC4.4 (AIN0), R68.2, R69.1
unnamed: C46.1, IC4.5 (AIN1), R66.2, R67.1
unnamed: C53.1, IC4.6 (AIN2), R82.2, R83.1
unnamed: C54.1, IC4.7 (AIN3), R84.2, R85.1
unnamed: P1.A5 (CC), R4.1
unnamed: P1.A6 (D+), P1.B6 (D+), R3.1
unnamed: P1.A7 (D-), P1.B7 (D-), R2.1
unnamed: P1.B5 (VCONN), R1.1
unnamed: Q1.2 (G), R71.1, R74.1
unnamed: Q2.2 (G), R72.1, R75.1
unnamed: Q3.2 (G), R73.1, R76.1
unnamed: R12.1, RV1.1
unnamed: R14.1, RV2.3
unnamed: R15.2, RV2.1
unnamed: R16.2, RV3.3
unnamed: R17.1, RV3.1
unnamed: R18.1, TEST.1, TEST.2
unnamed: R44.1, RV4.1
unnamed: R45.2, RV4.3
unnamed: R46.1, RV5.1
unnamed: R47.2, RV5.3
unnamed: C3.2, U1.7 (BST)
unnamed: C2.1, F1.2, U1.2 (VIN), U1.3 (EN_UVLO), V_in.1
unnamed: R9.1, U1.4 (RON)
unnamed: C3.1, D3.5, D3.6, D3.7, D3.8, L1.1, R13.1, U1.8 (SW)
unnamed: C12.1, U2.6 (BST)
unnamed: C14.2, RV3.2, U2.8 (FB)
unnamed: C10.1, U2.7 (SS)
unnamed: C12.2, L2.1, U2.5 (SW)
unnamed: C15.1, D5.1, D5.2, U3.2 (VO)
unnamed: C26.1, R22.1, R24.1, U6.6 (GPIO1/ADC1_CH0), Z4.1 (K)
unnamed: R28.1, U6.7 (GPIO2/ADC1_CH1)
unnamed: R26.1, U6.8 (GPIO3/ADC1_CH2)
unnamed: R29.1, U6.9 (GPIO4/ADC1_CH3)
unnamed: R27.1, U6.10 (GPIO5/ADC1_CH4)
unnamed: C29.1, R23.1, R25.2, U6.11 (GPIO6/ADC1_CH5), Z3.1 (K)
unnamed: R30.1, U6.18 (GPIO13/ADC2_CH2)
unnamed: R31.1, R86.2, U6.19 (GPIO14/ADC2_CH3)
unnamed: R36.2, U6.23 (GPIO17/ADC2_CH6)
unnamed: R35.2, U6.24 (GPIO18/ADC2_CH7)
unnamed: R34.2, U6.27 (GPIO21)
unnamed: R38.1, U6.39 (GPIO34)
unnamed: R39.1, U6.40 (GPIO35)
unnamed: R42.1, R43.1, U6.41 (GPIO36), Z7.1 (K)
unnamed: R32.1, U6.50 (U0RXD/PROG/GPIO44)
unnamed: R33.2, U6.49 (U0TXD/PROG/GPIO43)

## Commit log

2025-03-29 Initial commit
    s
2025-03-29 Copy almost complete pcb
2025-03-31 Backlink to CADLAB.io has been added.
